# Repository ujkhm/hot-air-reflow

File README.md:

# hot-air-reflow

A closed-loop hot-air reflow oven for double-sided SMT, built from scratch. The controller is an STM32F103C8T6. The mechanical model, control board, and firmware live in this repository.

#### 繁體中文說明在 [README.zh-TW.md](README.zh-TW.md)。

## Layout

```
hot-air-reflow
├── FreeCAD/        oven model (save the FCStd here)
├── KiCad/          control board
├── Code/STM32/     STM32CubeIDE + HAL firmware
└── scripts/        read coordinates from the FreeCAD model
```

The oven model is not in the repository yet. Save it under `FreeCAD/`.

## License

[MIT](LICENSE)

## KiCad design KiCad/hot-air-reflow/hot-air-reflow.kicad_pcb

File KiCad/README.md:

# KiCad

控制板用 KiCad 畫，專案檔放在這個資料夾。目標是 JLCPCB 雙層板，長寬都 ≤ 100 mm，控制器 STM32F103C8T6。

備份、快取和 `*.kicad_prl` 由 `.gitignore` 排除，跟其他專案同一套規則。

[回到主頁](../README.zh-TW.md)

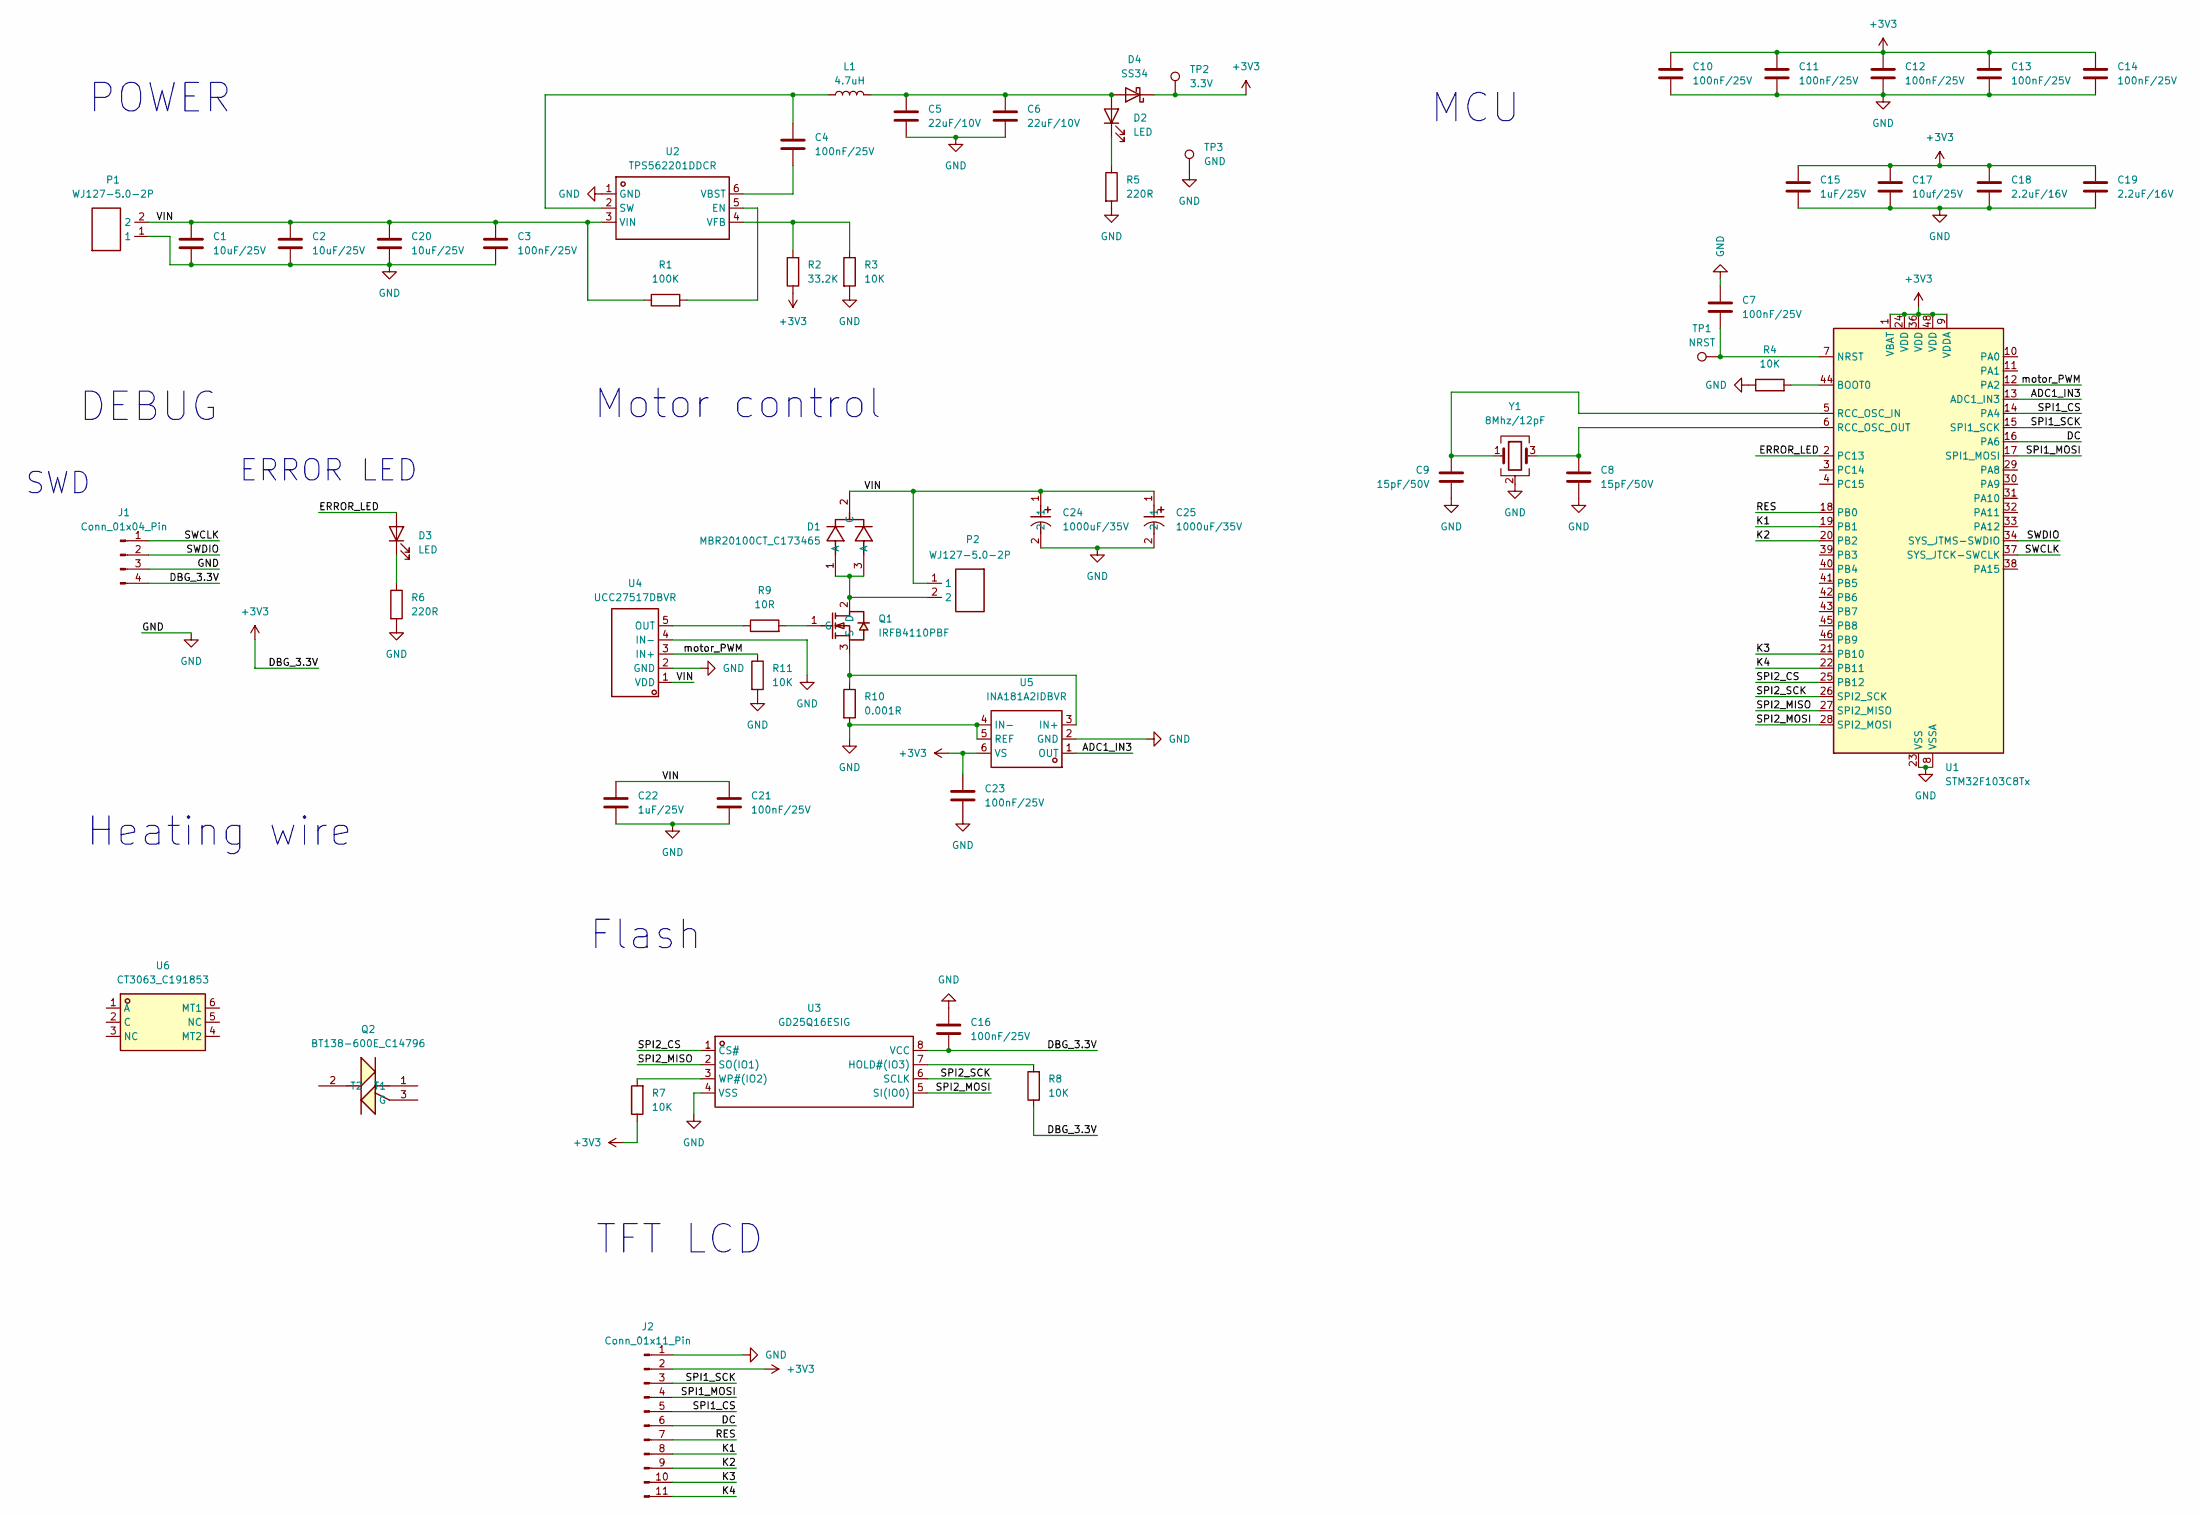
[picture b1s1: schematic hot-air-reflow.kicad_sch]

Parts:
C1, C2, C20: 10uF/25V; C_1206_3216Metric
C3, C4, C7, C10, C11, C12, C13, C14, C16, C21, C23: 100nF/25V; C_0603_1608Metric
C5, C6: 22uF/10V; C_1206_3216Metric
C8, C9: 15pF/50V; C_0603_1608Metric
C15, C22: 1uF/25V; C_0603_1608Metric
C17: 10uf/25V; C_0805_2012Metric
C18, C19: 2.2uF/16V; C_0603_1608Metric
C24, C25: 1000uF/35V; CAP-TH_BD10.0-P5.00-D1.0-FD; LCSC Part C49232884
D1: MBR20100CT_C173465; TO-220AB-3_L10.4-W4.6-P2.54-T; LCSC Part C173465
D2, D3: LED; LED_0603_1608Metric
D4: SS34; D_SMA
J1: Conn_01x04_Pin; PinHeader_1x04_P2.54mm_Vertical
J2: Conn_01x11_Pin; PinHeader_1x11_P2.54mm_Vertical
L1: 4.7uH; L_Bourns_SRP7028A_7.3x6.6mm
P1, P2: WJ127-5.0-2P; CONN-TH_2P-P5.00_CPC3703CTR; LCSC Part C3703
Q1: IRFB4110PBF; TO-220-3_L10.0-W4.5-P2.54-L; LCSC Part C2650
Q2: BT138-600E_C14796; TO-220-3_L10.0-W4.5-P2.54-L; LCSC Part C14796
R1: 100K; R_0603_1608Metric
R2: 33.2K; R_0603_1608Metric
R3, R4, R7, R8, R11: 10K; R_0603_1608Metric
R5, R6: 220R; R_0603_1608Metric
R9: 10R; R_0603_1608Metric
R10: 0.001R; R_2512_6332Metric
TP1: NRST; TestPoint_Pad_D1.5mm
TP2: 3.3V; TestPoint_Pad_D1.5mm
TP3: GND; TestPoint_Pad_D1.5mm
U1: STM32F103C8Tx; LQFP-48_7x7mm_P0.5mm
U2: TPS562201DDCR; SOT-23-6_L2.9-W1.6-P0.95-LS2.8-BR; LCSC Part C90061
U3: GD25Q16ESIG; SOP-8_L5.3-W5.3-P1.27-LS8.0-BL; LCSC Part C2693492
U4: UCC27517DBVR; SOT-23-5_L3.0-W1.7-P0.95-LS2.8-BR; LCSC Part C99395
U5: INA181A2IDBVR; SOT-23-6_L2.9-W1.6-P0.95-LS2.8-BL; LCSC Part C2058784
U6: CT3063_C191853; SOP-6_L7.1-W6.5-P2.54-LS10.1-BL; LCSC Part C191853
Y1: 8Mhz/12pF; Crystal_SMD_3225-4Pin_3.2x2.5mm

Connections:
+3V3: C10.1, C11.1, C12.1, C13.1, C14.1, C15.1, C16.2, C17.1, C18.1, C19.1, C23.1, D4.1 (K), J1.4, J2.2, R2.1, R7.1, R8.1, TP2.1, U1.1 (VBAT), U1.9 (VDDA), U1.24 (VDD), U1.36 (VDD), U1.48 (VDD), U3.8 (VCC), U5.6 (VS)
/ADC1_IN3: U1.13 (ADC1_IN3), U5.1 (OUT)
/DC: J2.6, U1.16 (PA6)
/ERROR_LED: D3.2 (A), U1.2 (PC13)
/K1: J2.8, U1.19 (PB1)
/K2: J2.9, U1.20 (PB2)
/K3: J2.10, U1.21 (PB10)
/K4: J2.11, U1.22 (PB11)
/RES: J2.7, U1.18 (PB0)
/SPI1_CS: J2.5, U1.14 (PA4)
/SPI1_MOSI: J2.4, U1.17 (SPI1_MOSI)
/SPI1_SCK: J2.3, U1.15 (SPI1_SCK)
/SPI2_CS: U1.25 (PB12), U3.1 (CS#)
/SPI2_MISO: U1.27 (SPI2_MISO), U3.2 (SO(IO1))
/SPI2_MOSI: U1.28 (SPI2_MOSI), U3.5 (SI(IO0))
/SPI2_SCK: U1.26 (SPI2_SCK), U3.6 (SCLK)
/SWCLK: J1.1, U1.37 (SYS_JTCK-SWCLK)
/SWDIO: J1.2, U1.34 (SYS_JTMS-SWDIO)
/VIN: C1.1, C2.1, C3.1, C20.1, C21.1, C22.1, C24.1, C25.1, D1.2 (C), P1.2, P2.1, R1.1, U2.3 (VIN), U4.1 (VDD)
/motor_PWM: R11.1, U1.12 (PA2), U4.3 (IN+)
GND: C1.2, C2.2, C3.2, C5.2, C6.2, C7.1, C8.2, C9.2, C10.2, C11.2, C12.2, C13.2, C14.2, C15.2, C16.1, C17.2, C18.2, C19.2, C20.2, C21.2, C22.2, C23.2, C24.2, C25.2, J1.3, J2.1, P1.1, R3.2, R4.1, R5.2, R6.2, R10.2, R11.2, TP3.1, U1.8 (VSSA), U1.23 (VSS), U1.35 (VSS), U1.47 (VSS), U2.1 (GND), U3.4 (VSS), U4.2 (GND), U4.4 (IN-), U5.2 (GND), U5.4 (IN-), U5.5 (REF), Y1.2 (G), Y1.4 (G)
unnamed: C5.1, C6.1, D2.2 (A), D4.2 (A), L1.2
unnamed: D2.1 (K), R5.1
unnamed: D3.1 (K), R6.1
unnamed: D1.1 (A), D1.3 (A), P2.2, Q1.2 (D)
unnamed: Q1.1 (G), R9.2
unnamed: Q1.3 (S), R10.1, U5.3 (IN+)
unnamed: R4.2, U1.44 (BOOT0)
unnamed: C7.2, TP1.1, U1.7 (NRST)
unnamed: C9.1, U1.5 (RCC_OSC_IN), Y1.1
unnamed: C8.1, U1.6 (RCC_OSC_OUT), Y1.3
unnamed: R1.2, U2.5 (EN)
unnamed: C4.1, L1.1, U2.2 (SW)
unnamed: C4.2, U2.6 (VBST)
unnamed: R2.2, R3.1, U2.4 (VFB)
unnamed: R8.2, U3.7 (HOLD#(IO3))
unnamed: R7.2, U3.3 (WP#(IO2))
unnamed: R9.1, U4.5 (OUT)

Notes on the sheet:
TFT LCD
Motor control
Flash
MCU
POWER
SWD
Heating wire
DEBUG
ERROR LED

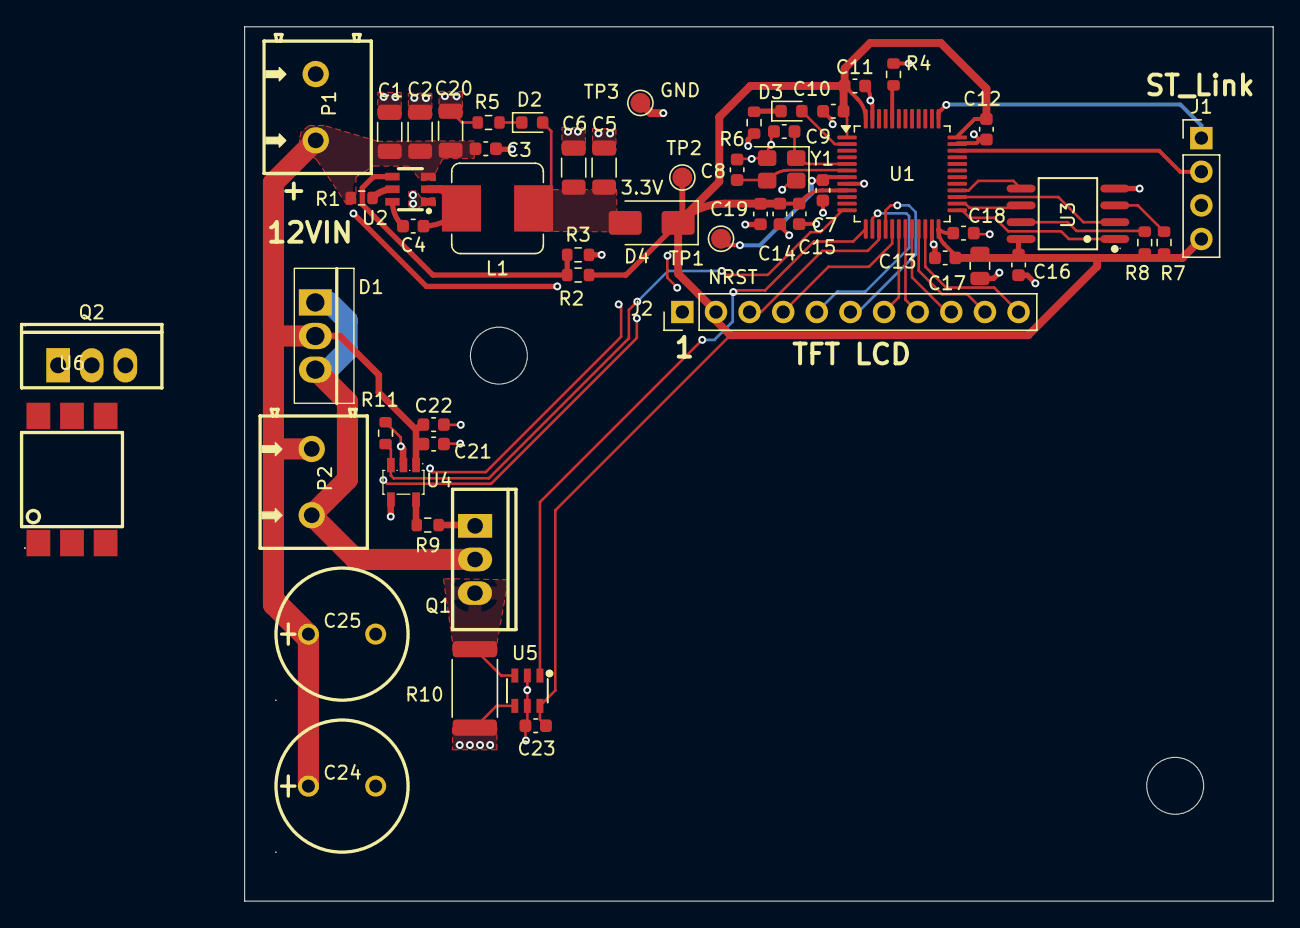
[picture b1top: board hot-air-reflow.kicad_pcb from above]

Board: 2 copper layers, 77.7 x 66.1 mm, 57 parts (0 on the bottom side), 38 nets.

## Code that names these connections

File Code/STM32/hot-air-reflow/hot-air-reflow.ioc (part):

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Mcu.Name=STM32F103C(8-B)Tx
Mcu.Package=LQFP48
Mcu.UserName=STM32F103C8Tx
PA13.Mode=Serial_Wire
PA13.Signal=SYS_JTMS-SWDIO
PA14.Mode=Serial_Wire
PA14.Signal=SYS_JTCK-SWCLK
PA2.Signal=GPIO_Output
PA3.Signal=ADCx_IN3
PA4.Signal=GPIO_Output
PA5.Mode=Simplex_Bidirectional_Master
PA5.Signal=SPI1_SCK
PA6.Signal=GPIO_Output
PA7.Mode=Simplex_Bidirectional_Master
PA7.Signal=SPI1_MOSI
PB1.Signal=GPIO_Input
PB10.Signal=GPIO_Input
PB11.Signal=GPIO_Input
PB13.Mode=Full_Duplex_Master
PB13.Signal=SPI2_SCK
PB14.Mode=Full_Duplex_Master
PB14.Signal=SPI2_MISO
PB15.Mode=Full_Duplex_Master
PB15.Signal=SPI2_MOSI
PB2.Signal=GPIO_Input
PB6.Mode=I2C
PB6.Signal=I2C1_SCL
PB7.Mode=I2C
PB7.Signal=I2C1_SDA
PC13-TAMPER-RTC.Signal=GPIO_Output
PD0-OSC_IN.Mode=HSE-External-Oscillator
PD0-OSC_IN.Signal=RCC_OSC_IN
PD1-OSC_OUT.Mode=HSE-External-Oscillator
PD1-OSC_OUT.Signal=RCC_OSC_OUT
RCC.SYSCLKFreq_VALUE=72000000
RCC.SYSCLKSource=RCC_SYSCLKSOURCE_PLLCLK
board=custom
